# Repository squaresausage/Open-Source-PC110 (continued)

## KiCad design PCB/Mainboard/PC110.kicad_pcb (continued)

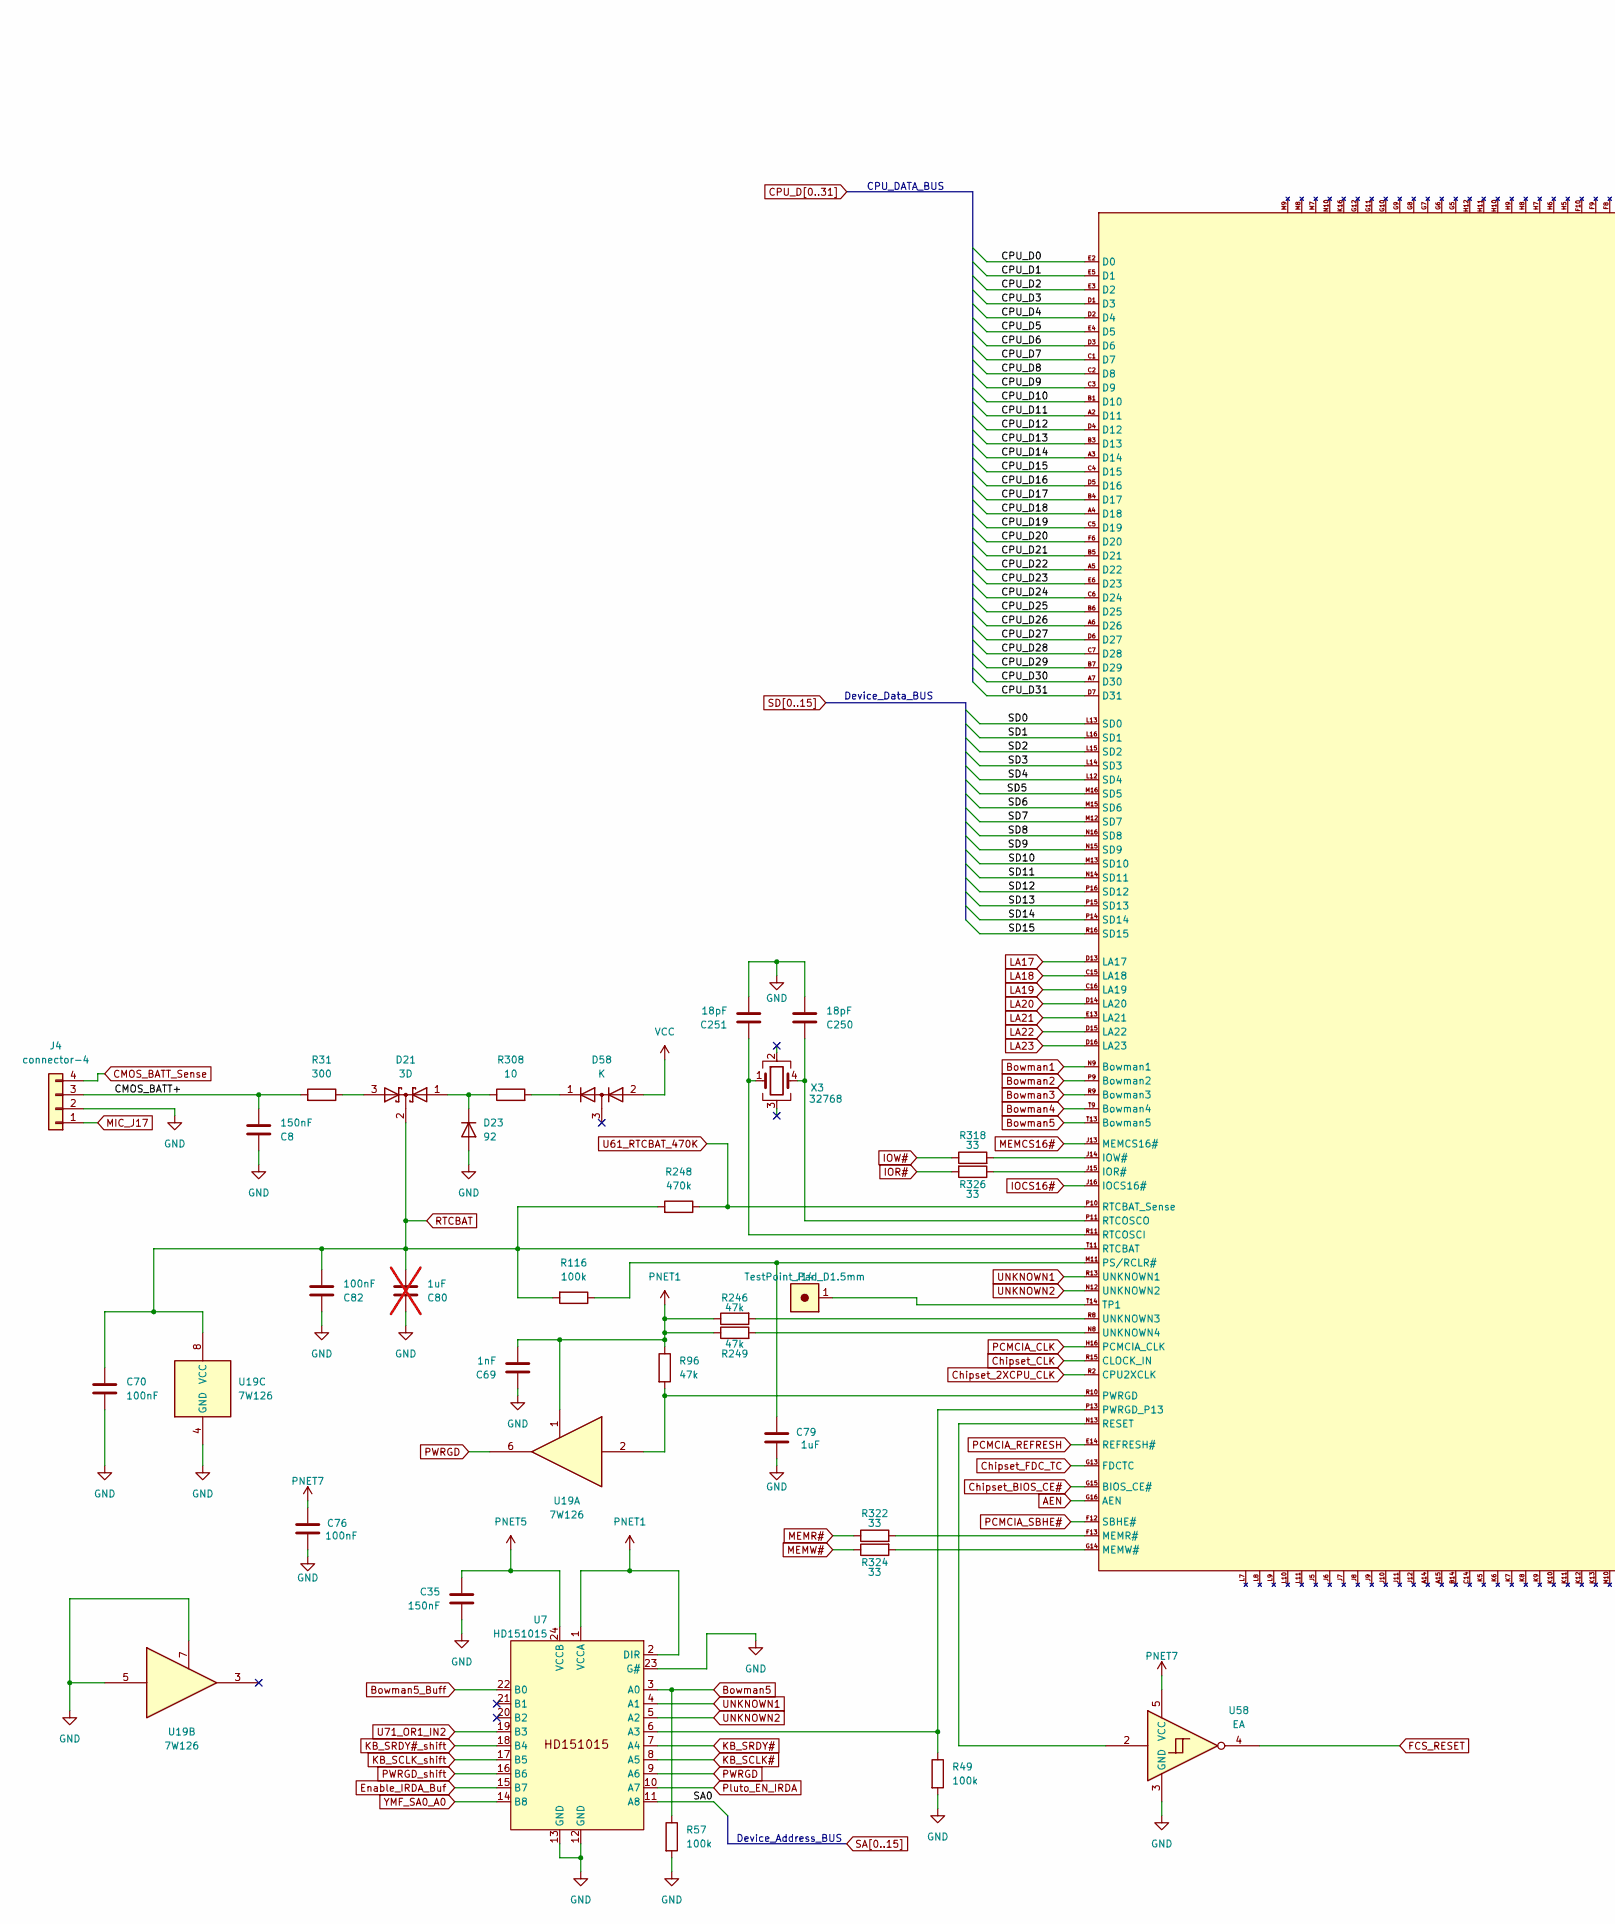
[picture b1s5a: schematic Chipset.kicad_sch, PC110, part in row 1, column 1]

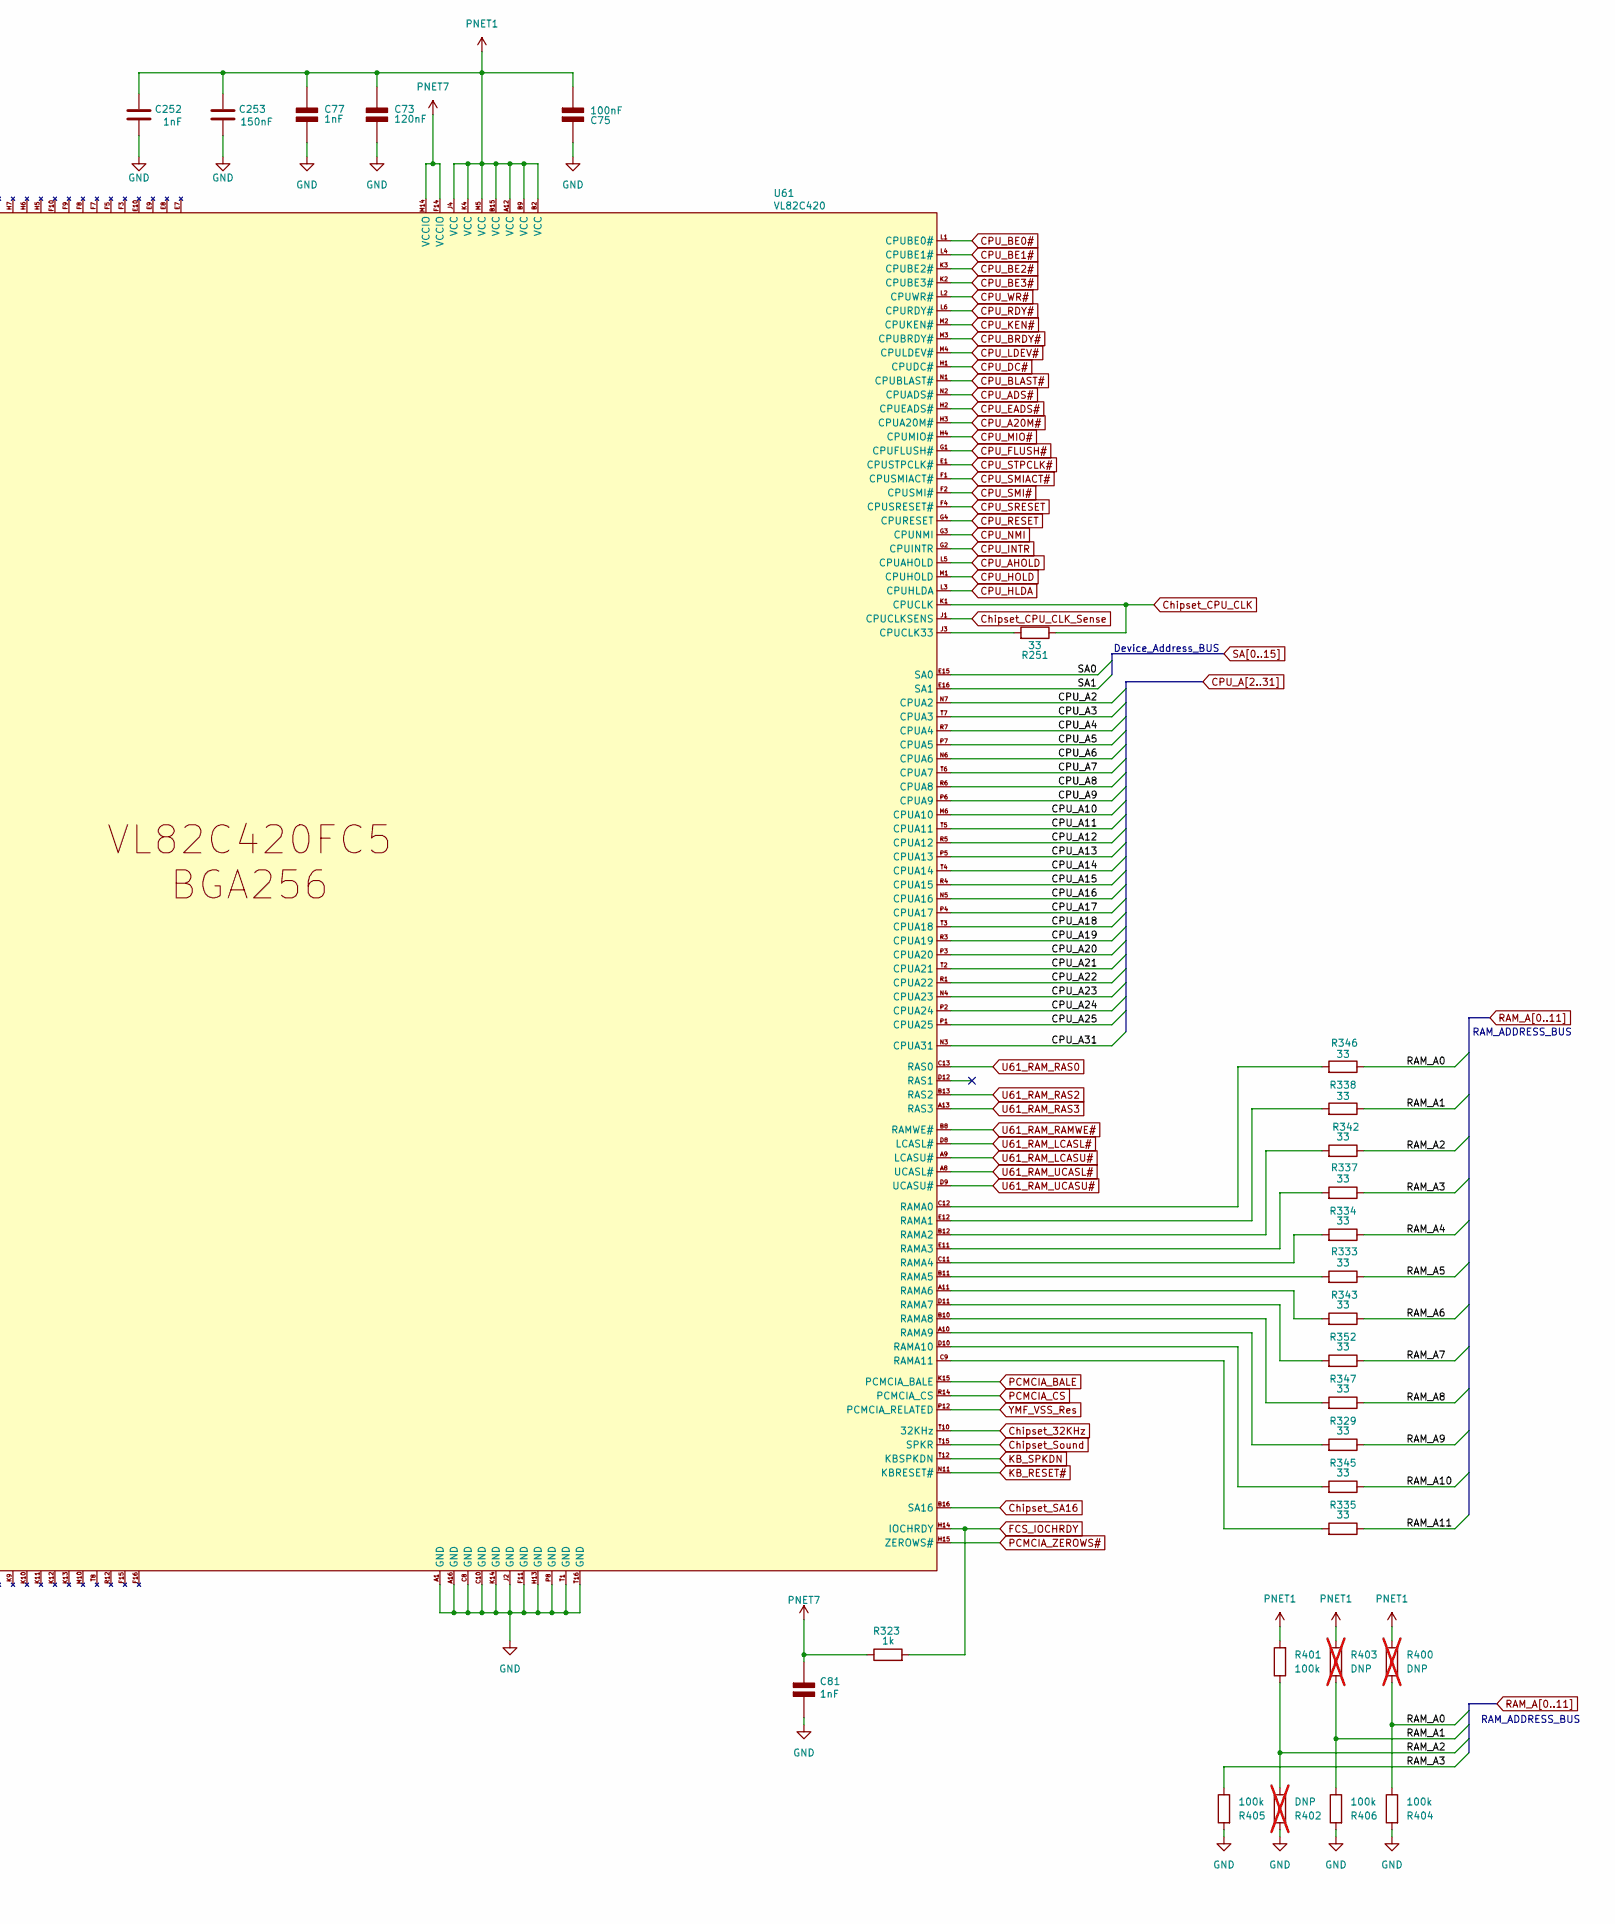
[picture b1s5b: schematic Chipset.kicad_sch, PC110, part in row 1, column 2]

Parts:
C8, C35, C253: 150nF; C_0402_1005Metric
C69, C77, C81, C252: 1nF; C_0402_1005Metric
C70, C75, C76, C82: 100nF; C_0402_1005Metric
C73: 120nF; C_0402_1005Metric
C79: 1uF; C_0603_1608Metric
C80: 1uF; C_0603_1608Metric; not fitted
C250, C251: 18pF; C_0402_1005Metric
D21: 3D
D23: 92; D_0603_1608Metric
D58: K; SOT-416L
J4: connector-4
J14: TestPoint_Pad_D1.5mm
R31: 300; R_0402_1005Metric
R49, R57, R116, R401, R404, R405, R406: 100k; R_0402_1005Metric
R96, R246, R249: 47k; R_0402_1005Metric
R248: 470k; R_0402_1005Metric
R251, R318, R322, R324, R326, R329, R333, R334, R335, R337, R338, R342, R343, R345, R346, R347, R352: 33; R_0402_1005Metric
R308: 10; R_0402_1005Metric
R323: 1k; R_0402_1005Metric
R400, R402, R403: DNP; R_0402_1005Metric; not fitted
U7: HD151015; TSSOP-24_6.1x7.8mm_P0.65mm
U19: 7W126; sso-8
U58: EA; SOT-353
U61: VL82C420; BGA-256
X3: 32768; XTAL-3

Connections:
/Chipset/CMOS_BATT+: C8.1, J4.3, R31.2
AEN: U61.G16 (AEN); also elsewhere on the board
Bowman1: U61.N9 (Bowman1); also elsewhere on the board
Bowman2: U61.P9 (Bowman2); also elsewhere on the board
Bowman3: U61.R9 (Bowman3); also elsewhere on the board
Bowman4: U61.T9 (Bowman4); also elsewhere on the board
Bowman5: R57.1, U7.3 (A0), U61.T13 (Bowman5); also elsewhere on the board
Bowman5_Buff: U7.22 (B0); also elsewhere on the board
CMOS_BATT_Sense: J4.4; also elsewhere on the board
CPU_A2: U61.N7 (CPUA2); also elsewhere on the board
CPU_A3: U61.T7 (CPUA3); also elsewhere on the board
CPU_A4: U61.R7 (CPUA4); also elsewhere on the board
CPU_A5: U61.P7 (CPUA5); also elsewhere on the board
CPU_A6: U61.N6 (CPUA6); also elsewhere on the board
CPU_A7: U61.T6 (CPUA7); also elsewhere on the board
CPU_A8: U61.R6 (CPUA8); also elsewhere on the board
CPU_A9: U61.P6 (CPUA9); also elsewhere on the board
CPU_A10: U61.M6 (CPUA10); also elsewhere on the board
CPU_A11: U61.T5 (CPUA11); also elsewhere on the board
CPU_A12: U61.R5 (CPUA12); also elsewhere on the board
CPU_A13: U61.P5 (CPUA13); also elsewhere on the board
CPU_A14: U61.T4 (CPUA14); also elsewhere on the board
CPU_A15: U61.R4 (CPUA15); also elsewhere on the board
CPU_A16: U61.N5 (CPUA16); also elsewhere on the board
CPU_A17: U61.P4 (CPUA17); also elsewhere on the board
CPU_A18: U61.T3 (CPUA18); also elsewhere on the board
CPU_A19: U61.R3 (CPUA19); also elsewhere on the board
CPU_A20: U61.P3 (CPUA20); also elsewhere on the board
CPU_A20M#: U61.H3 (CPUA20M#); also elsewhere on the board
CPU_A21: U61.T2 (CPUA21); also elsewhere on the board
CPU_A22: U61.R1 (CPUA22); also elsewhere on the board
CPU_A23: U61.N4 (CPUA23); also elsewhere on the board
CPU_A24: U61.P2 (CPUA24); also elsewhere on the board
CPU_A25: U61.P1 (CPUA25); also elsewhere on the board
CPU_A31: U61.N3 (CPUA31); also elsewhere on the board
CPU_ADS#: U61.N2 (CPUADS#); also elsewhere on the board
CPU_AHOLD: U61.L5 (CPUAHOLD); also elsewhere on the board
CPU_BE0#: U61.L1 (CPUBE0#); also elsewhere on the board
CPU_BE1#: U61.L4 (CPUBE1#); also elsewhere on the board
CPU_BE2#: U61.K3 (CPUBE2#); also elsewhere on the board
CPU_BE3#: U61.K2 (CPUBE3#); also elsewhere on the board
CPU_BLAST#: U61.N1 (CPUBLAST#); also elsewhere on the board
CPU_BRDY#: U61.M3 (CPUBRDY#); also elsewhere on the board
CPU_D0: U61.E2 (D0); also elsewhere on the board
CPU_D1: U61.E5 (D1); also elsewhere on the board
CPU_D2: U61.E3 (D2); also elsewhere on the board
CPU_D3: U61.D1 (D3); also elsewhere on the board
CPU_D4: U61.D2 (D4); also elsewhere on the board
CPU_D5: U61.E4 (D5); also elsewhere on the board
CPU_D6: U61.D3 (D6); also elsewhere on the board
CPU_D7: U61.C1 (D7); also elsewhere on the board
CPU_D8: U61.C2 (D8); also elsewhere on the board
CPU_D9: U61.C3 (D9); also elsewhere on the board
CPU_D10: U61.B1 (D10); also elsewhere on the board
CPU_D11: U61.A2 (D11); also elsewhere on the board
CPU_D12: U61.D4 (D12); also elsewhere on the board
CPU_D13: U61.B3 (D13); also elsewhere on the board
CPU_D14: U61.A3 (D14); also elsewhere on the board
CPU_D15: U61.C4 (D15); also elsewhere on the board
CPU_D16: U61.D5 (D16); also elsewhere on the board
CPU_D17: U61.B4 (D17); also elsewhere on the board
CPU_D18: U61.A4 (D18); also elsewhere on the board
CPU_D19: U61.C5 (D19); also elsewhere on the board
CPU_D20: U61.F6 (D20); also elsewhere on the board
CPU_D21: U61.B5 (D21); also elsewhere on the board
CPU_D22: U61.A5 (D22); also elsewhere on the board
CPU_D23: U61.E6 (D23); also elsewhere on the board
CPU_D24: U61.C6 (D24); also elsewhere on the board
CPU_D25: U61.B6 (D25); also elsewhere on the board
CPU_D26: U61.A6 (D26); also elsewhere on the board
CPU_D27: U61.D6 (D27); also elsewhere on the board
CPU_D28: U61.C7 (D28); also elsewhere on the board
CPU_D29: U61.B7 (D29); also elsewhere on the board
CPU_D30: U61.A7 (D30); also elsewhere on the board
CPU_D31: U61.D7 (D31); also elsewhere on the board
CPU_DC#: U61.H1 (CPUDC#); also elsewhere on the board
CPU_EADS#: U61.H2 (CPUEADS#); also elsewhere on the board
CPU_FLUSH#: U61.G1 (CPUFLUSH#); also elsewhere on the board
CPU_HLDA: U61.L3 (CPUHLDA); also elsewhere on the board
CPU_HOLD: U61.M1 (CPUHOLD); also elsewhere on the board
CPU_INTR: U61.G2 (CPUINTR); also elsewhere on the board
CPU_KEN#: U61.M2 (CPUKEN#); also elsewhere on the board
CPU_LDEV#: U61.M4 (CPULDEV#); also elsewhere on the board
CPU_MIO#: U61.H4 (CPUMIO#); also elsewhere on the board
CPU_NMI: U61.G3 (CPUNMI); also elsewhere on the board
CPU_RDY#: U61.L6 (CPURDY#); also elsewhere on the board
CPU_RESET: U61.G4 (CPURESET); also elsewhere on the board
CPU_SMI#: U61.F2 (CPUSMI#); also elsewhere on the board
CPU_SMIACT#: U61.F1 (CPUSMIACT#); also elsewhere on the board
CPU_SRESET: U61.F4 (CPUSRESET#); also elsewhere on the board
CPU_STPCLK#: U61.E1 (CPUSTPCLK#); also elsewhere on the board
CPU_WR#: U61.L2 (CPUWR#); also elsewhere on the board
Chipset_2XCPU_CLK: U61.R2 (CPU2XCLK); also elsewhere on the board
Chipset_32KHz: U61.T10 (32KHz); also elsewhere on the board
Chipset_BIOS_CE#: U61.G15 (BIOS_CE#); also elsewhere on the board
Chipset_CLK: U61.R15 (CLOCK_IN); also elsewhere on the board
Chipset_CPU_CLK: R251.1, U61.K1 (CPUCLK); also elsewhere on the board
Chipset_CPU_CLK_Sense: U61.J1 (CPUCLKSENS); also elsewhere on the board
Chipset_FDC_TC: U61.G13 (FDCTC); also elsewhere on the board
Chipset_SA16: U61.B16 (SA16); also elsewhere on the board
Chipset_Sound: U61.T15 (SPKR); also elsewhere on the board
Enable_IRDA_Buf: U7.15 (B7); also elsewhere on the board
FCS_IOCHRDY: R323.2, U61.H14 (IOCHRDY); also elsewhere on the board
FCS_RESET: U58.4; also elsewhere on the board
IOCS16#: U61.J16 (IOCS16#); also elsewhere on the board
IOR#: R326.2; also elsewhere on the board
IOW#: R318.1; also elsewhere on the board
KB_RESET#: U61.N11 (KBRESET#); also elsewhere on the board
KB_SCLK#: U7.8 (A5); also elsewhere on the board
KB_SCLK_shift: U7.17 (B5); also elsewhere on the board
KB_SPKDN: U61.T12 (KBSPKDN); also elsewhere on the board
KB_SRDY#: U7.7 (A4); also elsewhere on the board
KB_SRDY#_shift: U7.18 (B4); also elsewhere on the board
LA17: U61.D13 (LA17); also elsewhere on the board
LA18: U61.C15 (LA18); also elsewhere on the board
LA19: U61.C16 (LA19); also elsewhere on the board
LA20: U61.D14 (LA20); also elsewhere on the board
LA21: U61.E13 (LA21); also elsewhere on the board
LA22: U61.D15 (LA22); also elsewhere on the board
LA23: U61.D16 (LA23); also elsewhere on the board
MEMCS16#: U61.J13 (MEMCS16#); also elsewhere on the board
MEMR#: R322.1; also elsewhere on the board
MEMW#: R324.1; also elsewhere on the board
MIC_J17: J4.1; also elsewhere on the board
unnamed: D21.3 (A), R31.1
unnamed: D21.1 (A), D23.1 (K), R308.1
unnamed: D58.1 (K), R308.2
unnamed: R251.2, U61.J3 (CPUCLK33)
unnamed: R326.1, U61.J15 (IOR#)
unnamed: R318.2, U61.J14 (IOW#)
unnamed: R322.2, U61.F13 (MEMR#)
unnamed: R324.2, U61.G14 (MEMW#)
unnamed: C79.1, R116.1, U61.M11 (PS/RCLR#)
unnamed: R96.2, U19.2, U61.R10 (PWRGD)
unnamed: R49.1, U7.6 (A3), U61.P13 (PWRGD_P13)
unnamed: R346.2, U61.C12 (RAMA0)
unnamed: R338.2, U61.E12 (RAMA1)
unnamed: R342.2, U61.B12 (RAMA2)
unnamed: R337.2, U61.E11 (RAMA3)
unnamed: R334.2, U61.C11 (RAMA4)
unnamed: R333.2, U61.B11 (RAMA5)
unnamed: R343.2, U61.A11 (RAMA6)
unnamed: R352.2, U61.D11 (RAMA7)
unnamed: R347.2, U61.B10 (RAMA8)
unnamed: R329.2, U61.A10 (RAMA9)
unnamed: R345.2, U61.D10 (RAMA10)
unnamed: R335.2, U61.C9 (RAMA11)
unnamed: U58.2, U61.N13 (RESET)
unnamed: C251.2, U61.R11 (RTCOSCI), X3.1
unnamed: C250.2, U61.P11 (RTCOSCO), X3.4
unnamed: J14.1, U61.T14 (TP1)
unnamed: R246.2, U61.R8 (UNKNOWN3)
unnamed: R249.2, U61.N8 (UNKNOWN4)
PCMCIA_BALE: U61.K15 (PCMCIA_BALE); also elsewhere on the board
PCMCIA_CLK: U61.H16 (PCMCIA_CLK); also elsewhere on the board
PCMCIA_CS: U61.R14 (PCMCIA_CS); also elsewhere on the board
PCMCIA_REFRESH: U61.E14 (REFRESH#); also elsewhere on the board
PCMCIA_SBHE#: U61.F12 (SBHE#); also elsewhere on the board
PCMCIA_ZEROWS#: U61.H15 (ZEROWS#); also elsewhere on the board
PNET1: C69.1, C73.2 (-), C75.1 (+), C77.2 (-), C252.1, C253.1, R96.1, R246.1, R249.1, R400.2, R401.2, R403.2, U7.1 (VCCA), U7.2 (DIR), U19.1, U61.A12 (VCC), U61.B2 (VCC), U61.B9 (VCC), U61.B15 (VCC), U61.J4 (VCC), U61.K4 (VCC), U61.M5 (VCC); also elsewhere on the board
PNET7: C76.1, C81.1 (+), R323.1, U58.5 (VCC), U61.F14 (VCCIO), U61.M14 (VCCIO); also elsewhere on the board
PWRGD: U7.9 (A6), U19.6; also elsewhere on the board
PWRGD_shift: U7.16 (B6); also elsewhere on the board
Pluto_EN_IRDA: U7.10 (A7); also elsewhere on the board
RAM_A0: R346.1, R400.1, R404.1; also elsewhere on the board
RAM_A1: R338.1, R403.1, R406.1; also elsewhere on the board
RAM_A2: R342.1, R401.1, R402.1; also elsewhere on the board
RAM_A3: R337.1, R405.1; also elsewhere on the board
RAM_A4: R334.1; also elsewhere on the board
RAM_A5: R333.1; also elsewhere on the board
RAM_A6: R343.1; also elsewhere on the board
RAM_A7: R352.1; also elsewhere on the board
RAM_A8: R347.1; also elsewhere on the board
RAM_A9: R329.1; also elsewhere on the board
RAM_A10: R345.1; also elsewhere on the board
RAM_A11: R335.1; also elsewhere on the board
RTCBAT: C70.2, C80.1, C82.1, D21.2 (K), R116.2, R248.2, U19.8 (VCC), U61.T11 (RTCBAT); also elsewhere on the board
SA0: U7.11 (A8), U61.E15 (SA0); also elsewhere on the board
SA1: U61.E16 (SA1); also elsewhere on the board
SD0: U61.L13 (SD0); also elsewhere on the board
SD1: U61.L16 (SD1); also elsewhere on the board
SD2: U61.L15 (SD2); also elsewhere on the board
SD3: U61.L14 (SD3); also elsewhere on the board
SD4: U61.L12 (SD4); also elsewhere on the board
SD5: U61.M16 (SD5); also elsewhere on the board
SD6: U61.M15 (SD6); also elsewhere on the board
SD7: U61.M12 (SD7); also elsewhere on the board
SD8: U61.N16 (SD8); also elsewhere on the board
SD9: U61.N15 (SD9); also elsewhere on the board
SD10: U61.M13 (SD10); also elsewhere on the board
SD11: U61.N14 (SD11); also elsewhere on the board
SD12: U61.P16 (SD12); also elsewhere on the board
SD13: U61.P15 (SD13); also elsewhere on the board
SD14: U61.P14 (SD14); also elsewhere on the board
SD15: U61.R16 (SD15); also elsewhere on the board
U61_RAM_LCASL#: U61.D8 (LCASL#); also elsewhere on the board
U61_RAM_LCASU#: U61.A9 (LCASU#); also elsewhere on the board
U61_RAM_RAMWE#: U61.B8 (RAMWE#); also elsewhere on the board
U61_RAM_RAS0: U61.C13 (RAS0); also elsewhere on the board
U61_RAM_RAS2: U61.B13 (RAS2); also elsewhere on the board
U61_RAM_RAS3: U61.A13 (RAS3); also elsewhere on the board
U61_RAM_UCASL#: U61.A8 (UCASL#); also elsewhere on the board
U61_RAM_UCASU#: U61.D9 (UCASU#); also elsewhere on the board
U61_RTCBAT_470K: R248.1, U61.P10 (RTCBAT_Sense); also elsewhere on the board
U71_OR1_IN2: U7.19 (B3); also elsewhere on the board
UNKNOWN1: U7.4 (A1), U61.R13 (UNKNOWN1)
UNKNOWN2: U7.5 (A2), U61.N12 (UNKNOWN2)
VCC: D58.2 (A); also elsewhere on the board
YMF_SA0_A0: U7.14 (B8); also elsewhere on the board
YMF_VSS_Res: U61.P12 (PCMCIA_RELATED); also elsewhere on the board

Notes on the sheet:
CPU_DATA_BUS
Device_Data_BUS
Device_Address_BUS
RAM_ADDRESS_BUS
